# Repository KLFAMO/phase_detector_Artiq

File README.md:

# Phase Detector for Frequencies from 0 to 200 MHz

## Description

This is a phase detector designed to measure phase differences for input frequencies ranging from 0 to approximately 200 MHz. The device includes configurable frequency dividers for each input channel.

An STM32 microcontroller is used to manage the operational parameters of the detector and its components. These settings can be modified via an Ethernet interface by sending specific commands to the device.

## Features

- **Frequency Range**: 0 - 200 MHz (may change, depending on chips availability)
- **Configurable Frequency Dividers** for each input channel
- **STM32 Microcontroller** to manage operational parameters
- **Ethernet Communication** for real-time configuration and monitoring
- **Outputs**:
  - Fast analog output from the phase detector
  - Slow analog output from the phase detector
  - Analog output after passing through a PI controller
- **Standards**: The device is compliant with **Sinara** and **Artic** standards, ensuring compatibility with other systems that adhere to these protocols.

## Communication

The device allows full configuration and monitoring via Ethernet. Users can send commands to the microcontroller to change parameters such as:
- Frequency divider values
- Phase detector settings
- Calibration and diagnostics

## Applications

The phase detector is suitable for a variety of applications, including:
- Laser to optical frequency comb frequency locking
- Laser to laser frequency locking.

## Documentation

Detailed documentation, including schematics, source code, and configuration instructions, will be provided in future releases of the repository.

## commands

`R 1` - read register from `ADDR`, after reading `R` is set to 0

`W 1` - write to register of address `ADDR`, after writing `W` is set to 0

`RV` - red value

`WV` - value to write 

`ADDR` - register address to be red or written

## License

[MIT](https://opensource.org/licenses/MIT)

## Acknowledgments
This work has received funding from the European Partnership on Metrology, co-financed by the European Union’s Horizon Europe Research and Innovation Programme and by the Participating States, under grant number 22IEM01 TOCK.

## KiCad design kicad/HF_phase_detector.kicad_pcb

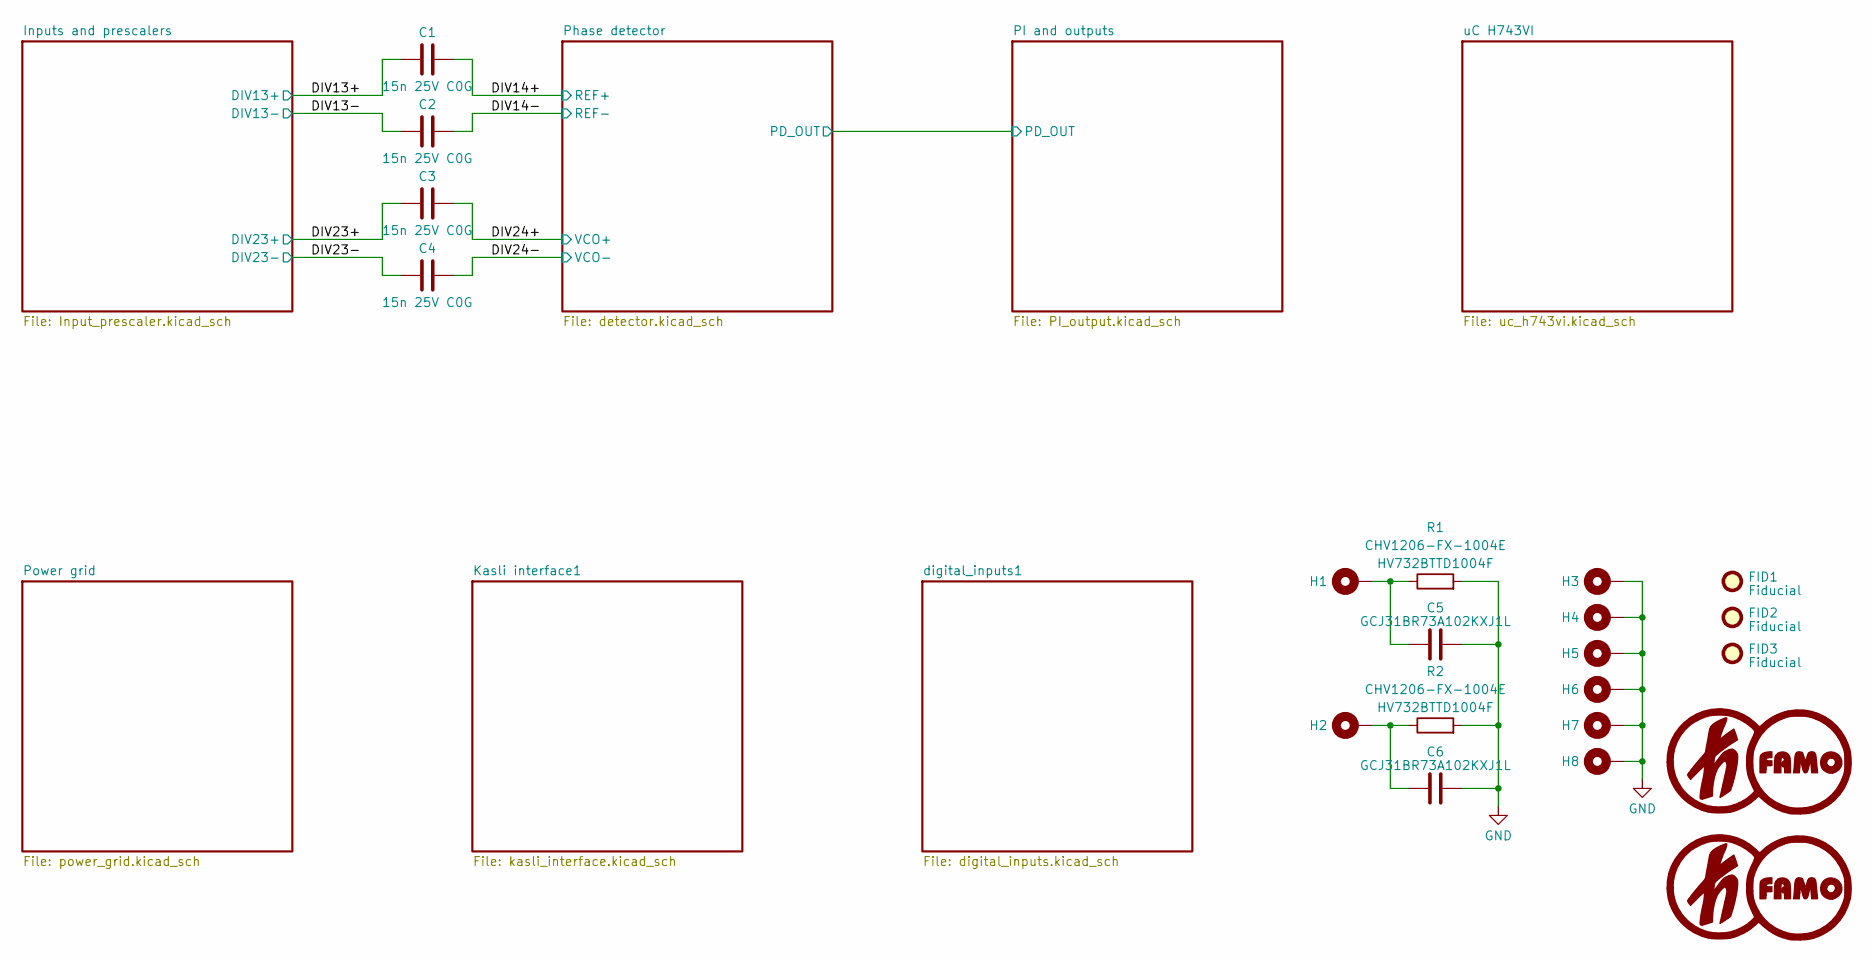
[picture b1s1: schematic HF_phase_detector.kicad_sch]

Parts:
C1, C2, C3, C4: 15n 25V C0G; C_0603_1608Metric
C5, C6: GCJ31BR73A102KXJ1L; C_1206_3216Metric
FID1, FID2, FID3: Fiducial; Fiducial_0.5mm_Mask1.5mm
G1, G2: LOGO; kl_famo_logo_small
H1, H2: MountingHole_Pad; MountingHole_2.7mm_M2.5_DIN965_Pad
H3, H4, H5, H6, H7, H8: MountingHole_Pad; MountingHole_3.2mm_M3_DIN965_Pad
R1, R2: CHV1206-FX-1004E; R_1206_3216Metric

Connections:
/DIV13-: C2.2; also elsewhere on the board
/DIV14-: C2.1; also elsewhere on the board
/DIV23+: C3.2; also elsewhere on the board
/DIV23-: C4.2; also elsewhere on the board
/DIV24+: C3.1; also elsewhere on the board
/DIV24-: C4.1; also elsewhere on the board
unnamed: C5.1, H1.1, R1.1
unnamed: C6.1, H2.1, R2.1

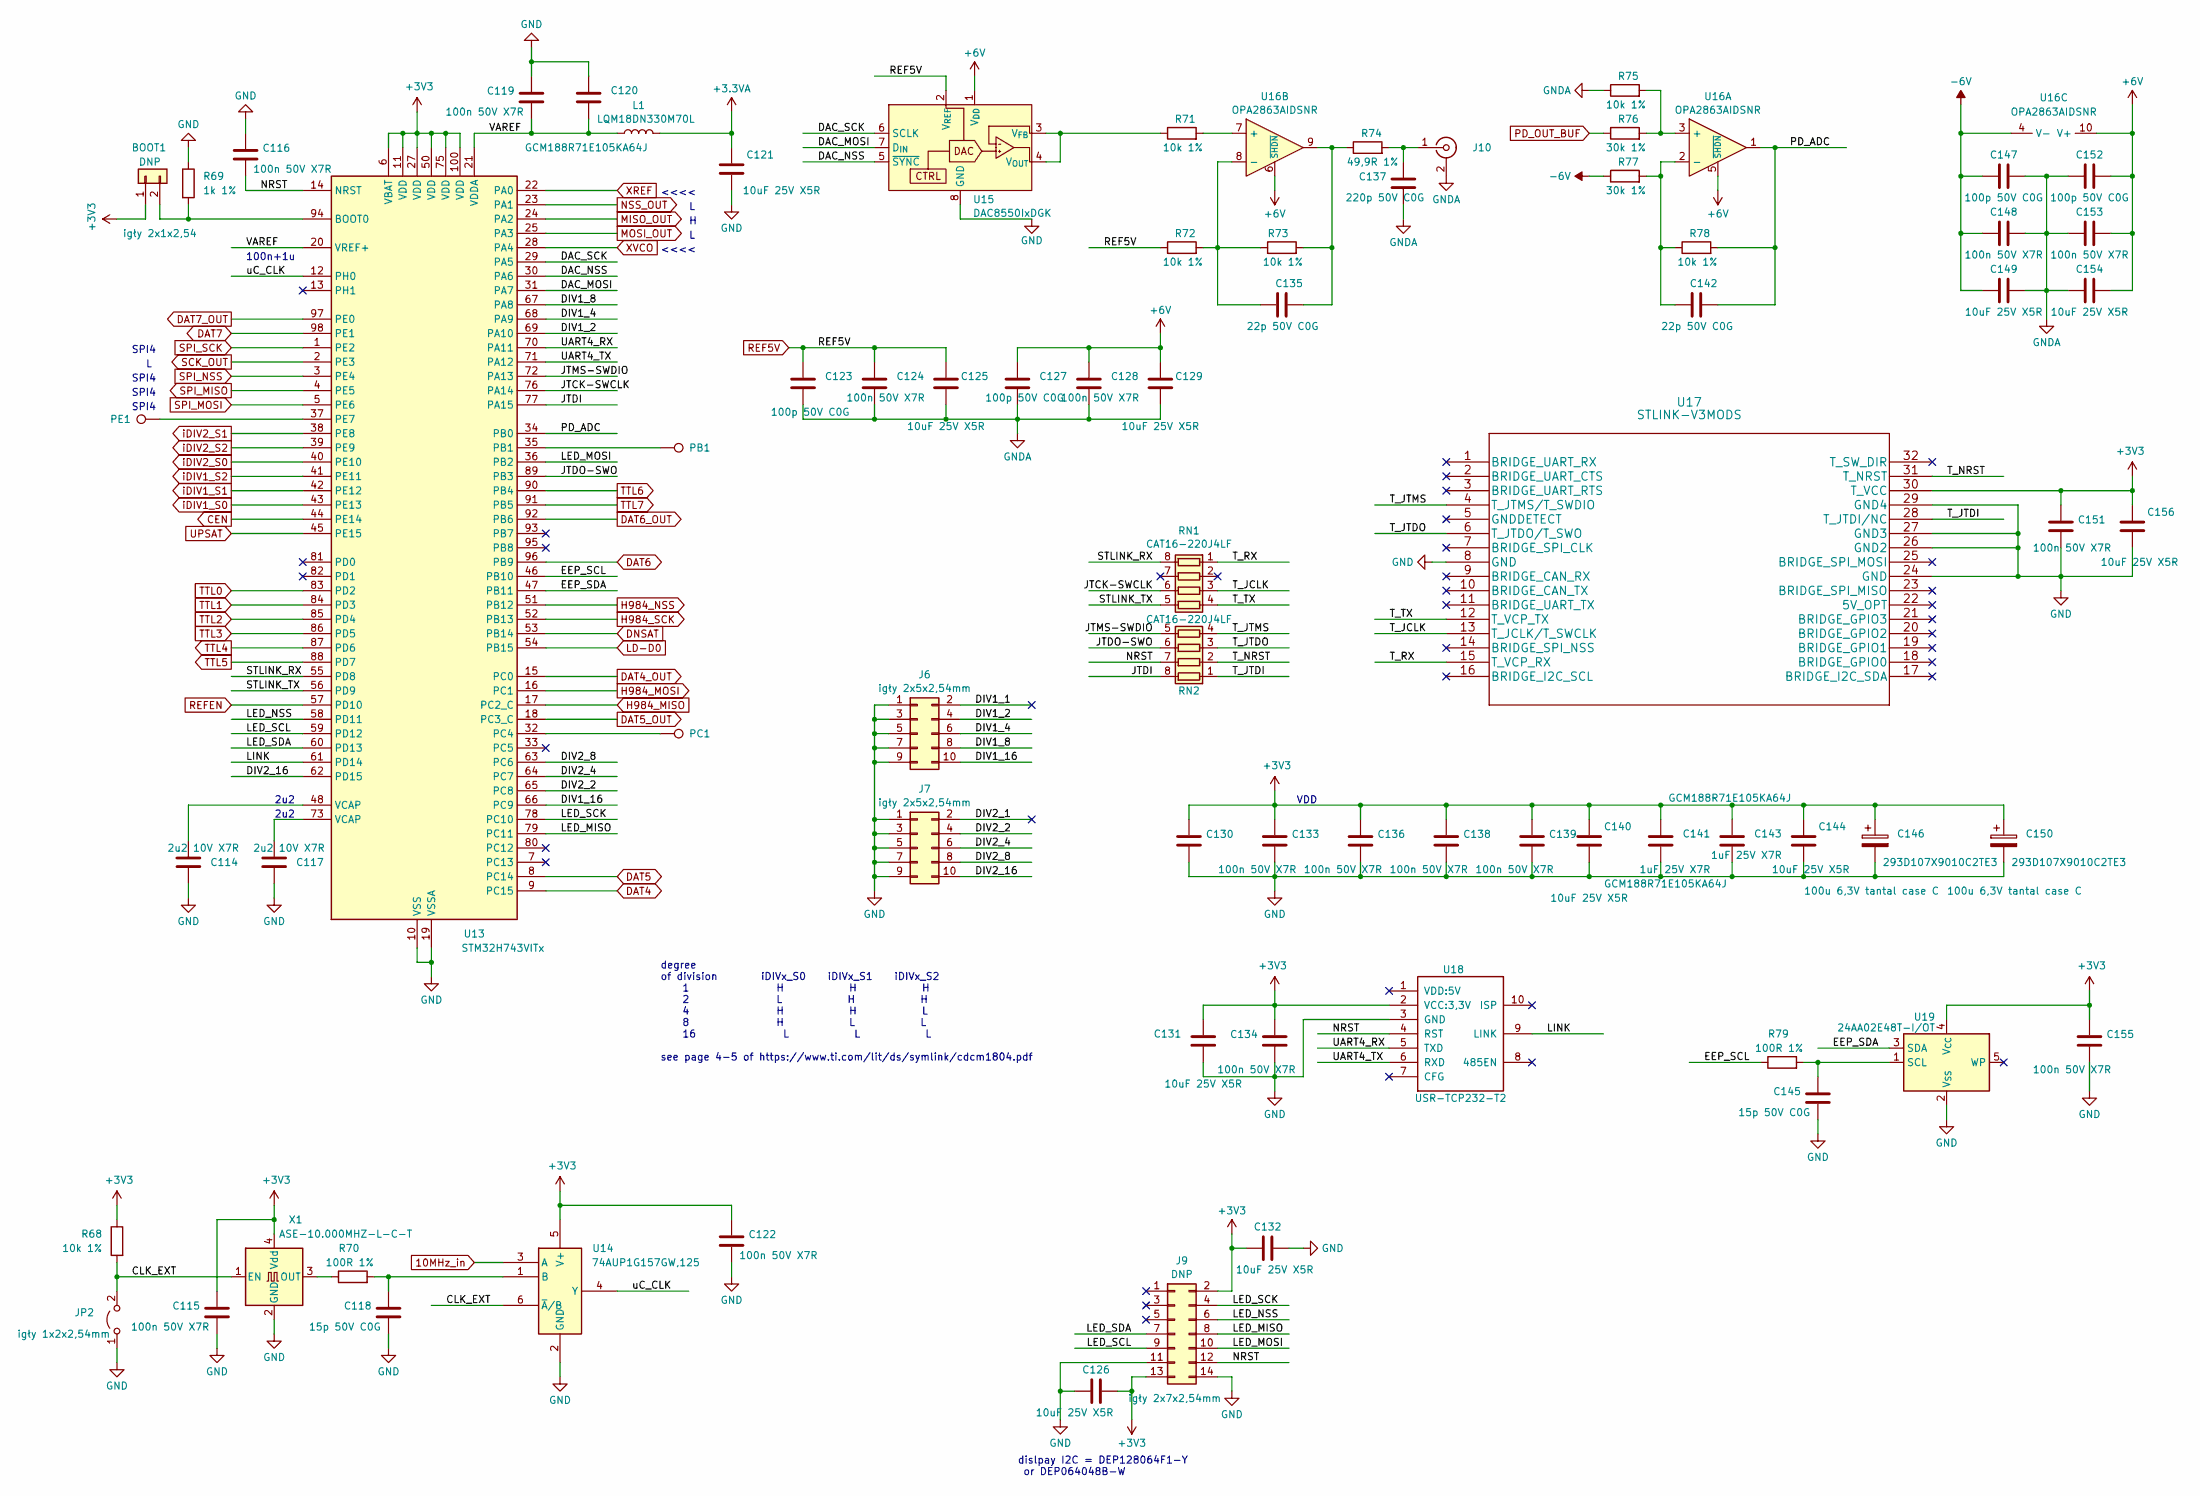
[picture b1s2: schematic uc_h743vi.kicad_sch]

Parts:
BOOT1: DNP; PinHeader_1x02_P2.54mm_Vertical
C114, C117: 2u2 10V X7R; C_0603_1608Metric
C115, C116, C119, C122, C124, C128, C130, C133, C134, C136, C138, C139, C148, C151, C153, C155: 100n 50V X7R; C_0603_1608Metric
C118, C145: 15p 50V C0G; C_0603_1608Metric
C120, C141, C143: GCM188R71E105KA64J; C_0603_1608Metric
C121, C125, C126, C129, C131, C132, C140, C144, C149, C154, C156: GRM188R61E106KA73; C_0603_1608Metric
C123, C127, C147, C152: 100p 50V C0G; C_0603_1608Metric
C135, C142: 22p 50V C0G; C_0603_1608Metric
C137: 220p 50V C0G; C_0603_1608Metric
C146, C150: 293D107X9010C2TE3; CP_EIA-7132-28_AVX-C
J6, J7: igły 2x5x2,54mm; PinHeader_2x05_P2.54mm_Vertical
J9: DNP; PinHeader_2x07_P2.54mm_Vertical
J10: SMA6251A1-3GT50G-50; SMA_Amphenol_132291-12_Vertical
JP2: igły 1x2x2,54mm; PinHeader_1x02_P2.54mm_Vertical
L1: LQM18DN330M70L; L_0603_1608Metric
PB1: TestPoint; TestPoint_THTPad_D1.0mm_Drill0.5mm
PC1: TestPoint; TestPoint_THTPad_D1.0mm_Drill0.5mm
PE1: TestPoint; TestPoint_THTPad_D1.0mm_Drill0.5mm
R68, R71, R72, R73, R75, R78: 10k 1%; R_0603_1608Metric
R69: 1k 1%; R_0603_1608Metric
R70, R79: 100R 1%; R_0603_1608Metric
R74: 49,9R 1%; R_0603_1608Metric
R76, R77: 30k 1%; R_0603_1608Metric
RN1, RN2: CAT16-220J4LF; R_Array_Concave_4x0603
U13: STM32H743VITx; LQFP-100_14x14mm_P0.5mm
U14: 74AUP1G157GW,125; SOT-363_SC-70-6
U15: DAC8550IxDGK; MSOP-8_3x3mm_P0.65mm
U16: OPA2863AIDSNR; DFN-10-1EP_3x3mm_P0.5mm_EP1.65x2.38mm_ThermalVias
U17: STLINK-V3MODS
U18: USR-TCP232-T2; USR-TC232-T2
U19: 24AA02E48T-I/OT; SOT-23-5
X1: ASE-10.000MHZ-L-C-T; Oscillator_SMD_Abracon_ASE-4Pin_3.2x2.5mm

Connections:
10MHz_in: U14.3 (A); also elsewhere on the board
/uC H743VI/CLK_EXT: JP2.2 (B), R68.2, U14.6 (~A/B), X1.1 (EN)
/uC H743VI/DAC_MOSI: U13.31 (PA7), U15.7 (D_{IN})
/uC H743VI/DAC_NSS: U13.30 (PA6), U15.5 (~SYNC)
/uC H743VI/DAC_SCK: U13.29 (PA5), U15.6 (SCLK)
/uC H743VI/DIV1_1: J6.2
/uC H743VI/DIV1_2: J6.4, U13.69 (PA10)
/uC H743VI/DIV1_4: J6.6, U13.68 (PA9)
/uC H743VI/DIV1_8: J6.8, U13.67 (PA8)
/uC H743VI/DIV1_16: J6.10, U13.66 (PC9)
/uC H743VI/DIV2_1: J7.2
/uC H743VI/DIV2_2: J7.4, U13.65 (PC8)
/uC H743VI/DIV2_4: J7.6, U13.64 (PC7)
/uC H743VI/DIV2_8: J7.8, U13.63 (PC6)
/uC H743VI/DIV2_16: J7.10, U13.62 (PD15)
/uC H743VI/EEP_SCL: R79.1, U13.46 (PB10)
/uC H743VI/EEP_SDA: U13.47 (PB11), U19.3 (SDA)
/uC H743VI/JTCK-SWCLK: RN1.6 (R3.2), U13.76 (PA14)
/uC H743VI/JTDI: RN2.8 (R1.2), U13.77 (PA15)
/uC H743VI/JTDO-SWO: RN2.6 (R3.2), U13.89 (PB3)
/uC H743VI/JTMS-SWDIO: RN2.5 (R4.2), U13.72 (PA13)
/uC H743VI/LED_MISO: J9.8, U13.79 (PC11)
/uC H743VI/LED_MOSI: J9.10, U13.36 (PB2)
/uC H743VI/LED_NSS: J9.6, U13.58 (PD11)
/uC H743VI/LED_SCK: J9.4, U13.78 (PC10)
/uC H743VI/LED_SCL: J9.9, U13.59 (PD12)
/uC H743VI/LED_SDA: J9.7, U13.60 (PD13)
/uC H743VI/LINK: U13.61 (PD14), U18.9 (LINK)
/uC H743VI/NRST: C116.2, J9.12, RN2.7 (R2.2), U13.14 (NRST), U18.4 (RST)
/uC H743VI/STLINK_RX: RN1.8 (R1.2), U13.55 (PD8)
/uC H743VI/STLINK_TX: RN1.5 (R4.2), U13.56 (PD9)
/uC H743VI/T_JCLK: RN1.3 (R3.1), U17.13 (T_JCLK/T_SWCLK)
/uC H743VI/T_JTDI: RN2.1 (R1.1), U17.28 (T_JTDI/NC)
/uC H743VI/T_JTDO: RN2.3 (R3.1), U17.6 (T_JTDO/T_SWO)
/uC H743VI/T_JTMS: RN2.4 (R4.1), U17.4 (T_JTMS/T_SWDIO)
/uC H743VI/T_NRST: RN2.2 (R2.1), U17.31 (T_NRST)
/uC H743VI/T_RX: RN1.1 (R1.1), U17.15 (T_VCP_RX)
/uC H743VI/T_TX: RN1.4 (R4.1), U17.12 (T_VCP_TX)
/uC H743VI/UART4_RX: U13.70 (PA11), U18.5 (TXD)
/uC H743VI/UART4_TX: U13.71 (PA12), U18.6 (RXD)
/uC H743VI/uC_CLK: U13.12 (PH0), U14.4 (Y)
CEN: U13.44 (PE14); also elsewhere on the board
DAT4: U13.9 (PC15); also elsewhere on the board
DAT4_OUT: U13.15 (PC0); also elsewhere on the board
DAT5: U13.8 (PC14); also elsewhere on the board
DAT5_OUT: U13.18 (PC3_C); also elsewhere on the board
DAT6: U13.96 (PB9); also elsewhere on the board
DAT6_OUT: U13.92 (PB6); also elsewhere on the board
DAT7: U13.98 (PE1); also elsewhere on the board
DAT7_OUT: U13.97 (PE0); also elsewhere on the board
DNSAT: U13.53 (PB14); also elsewhere on the board
H984_MISO: U13.17 (PC2_C); also elsewhere on the board
H984_MOSI: U13.16 (PC1); also elsewhere on the board
H984_NSS: U13.51 (PB12); also elsewhere on the board
H984_SCK: U13.52 (PB13); also elsewhere on the board
LD-D0: U13.54 (PB15); also elsewhere on the board
MISO_OUT: U13.24 (PA2); also elsewhere on the board
MOSI_OUT: U13.25 (PA3); also elsewhere on the board
NSS_OUT: U13.23 (PA1); also elsewhere on the board
unnamed: BOOT1.2, R69.2, U13.94 (BOOT0)
unnamed: C114.2, U13.48 (VCAP)
unnamed: C117.2, U13.73 (VCAP)
unnamed: C135.2, R73.2, R74.1, U16.9
unnamed: C137.2, J10.1 (In), R74.2
unnamed: PB1.1, U13.35 (PB1)
unnamed: PC1.1, U13.32 (PC4)
unnamed: PE1.1, U13.37 (PE7)
unnamed: C118.1, R70.2, U14.1 (B)
unnamed: R71.1, U15.3 (V_{FB}), U15.4 (V_{OUT})
unnamed: R75.2, R76.2, U16.3 (+)
unnamed: R71.2, U16.7 (+)
unnamed: C135.1, R72.2, R73.1, U16.8 (-)
unnamed: C145.1, R79.2, U19.1 (SCL)
unnamed: R70.1, X1.3 (OUT)
PD_OUT_BUF: R76.1; also elsewhere on the board
REF5V: C123.2, C124.2, C125.2, R72.1, U15.2 (V_{REF}); also elsewhere on the board
REFEN: U13.57 (PD10); also elsewhere on the board
SCK_OUT: U13.2 (PE3); also elsewhere on the board
SPI_MISO: U13.4 (PE5); also elsewhere on the board
SPI_MOSI: U13.5 (PE6); also elsewhere on the board
SPI_NSS: U13.3 (PE4); also elsewhere on the board
SPI_SCK: U13.1 (PE2); also elsewhere on the board
TTL0: U13.83 (PD2); also elsewhere on the board
TTL1: U13.84 (PD3); also elsewhere on the board
TTL2: U13.85 (PD4); also elsewhere on the board
TTL3: U13.86 (PD5); also elsewhere on the board
TTL4: U13.87 (PD6); also elsewhere on the board
TTL5: U13.88 (PD7); also elsewhere on the board
TTL6: U13.90 (PB4); also elsewhere on the board
TTL7: U13.91 (PB5); also elsewhere on the board
UPSAT: U13.45 (PE15); also elsewhere on the board
XREF: U13.22 (PA0); also elsewhere on the board
XVCO: U13.28 (PA4); also elsewhere on the board
iDIV1_S0: U13.43 (PE13); also elsewhere on the board
iDIV1_S1: U13.42 (PE12); also elsewhere on the board
iDIV1_S2: U13.41 (PE11); also elsewhere on the board
iDIV2_S0: U13.40 (PE10); also elsewhere on the board
iDIV2_S1: U13.38 (PE8); also elsewhere on the board
iDIV2_S2: U13.39 (PE9); also elsewhere on the board

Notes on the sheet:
VDD
2u2
<<<<
dislpay I2C = DEP128064F1-Y or DEP064048B-W
SPI4
100n+1u
degree of division iDIVx_S0 iDIVx_S1 iDIVx_S2 1 H H H 2 L H H 4 H H L 8 H L L 16 L L L see page 4-5 of https://www.ti.com/lit/ds/symlink/cdcm1804.pdf

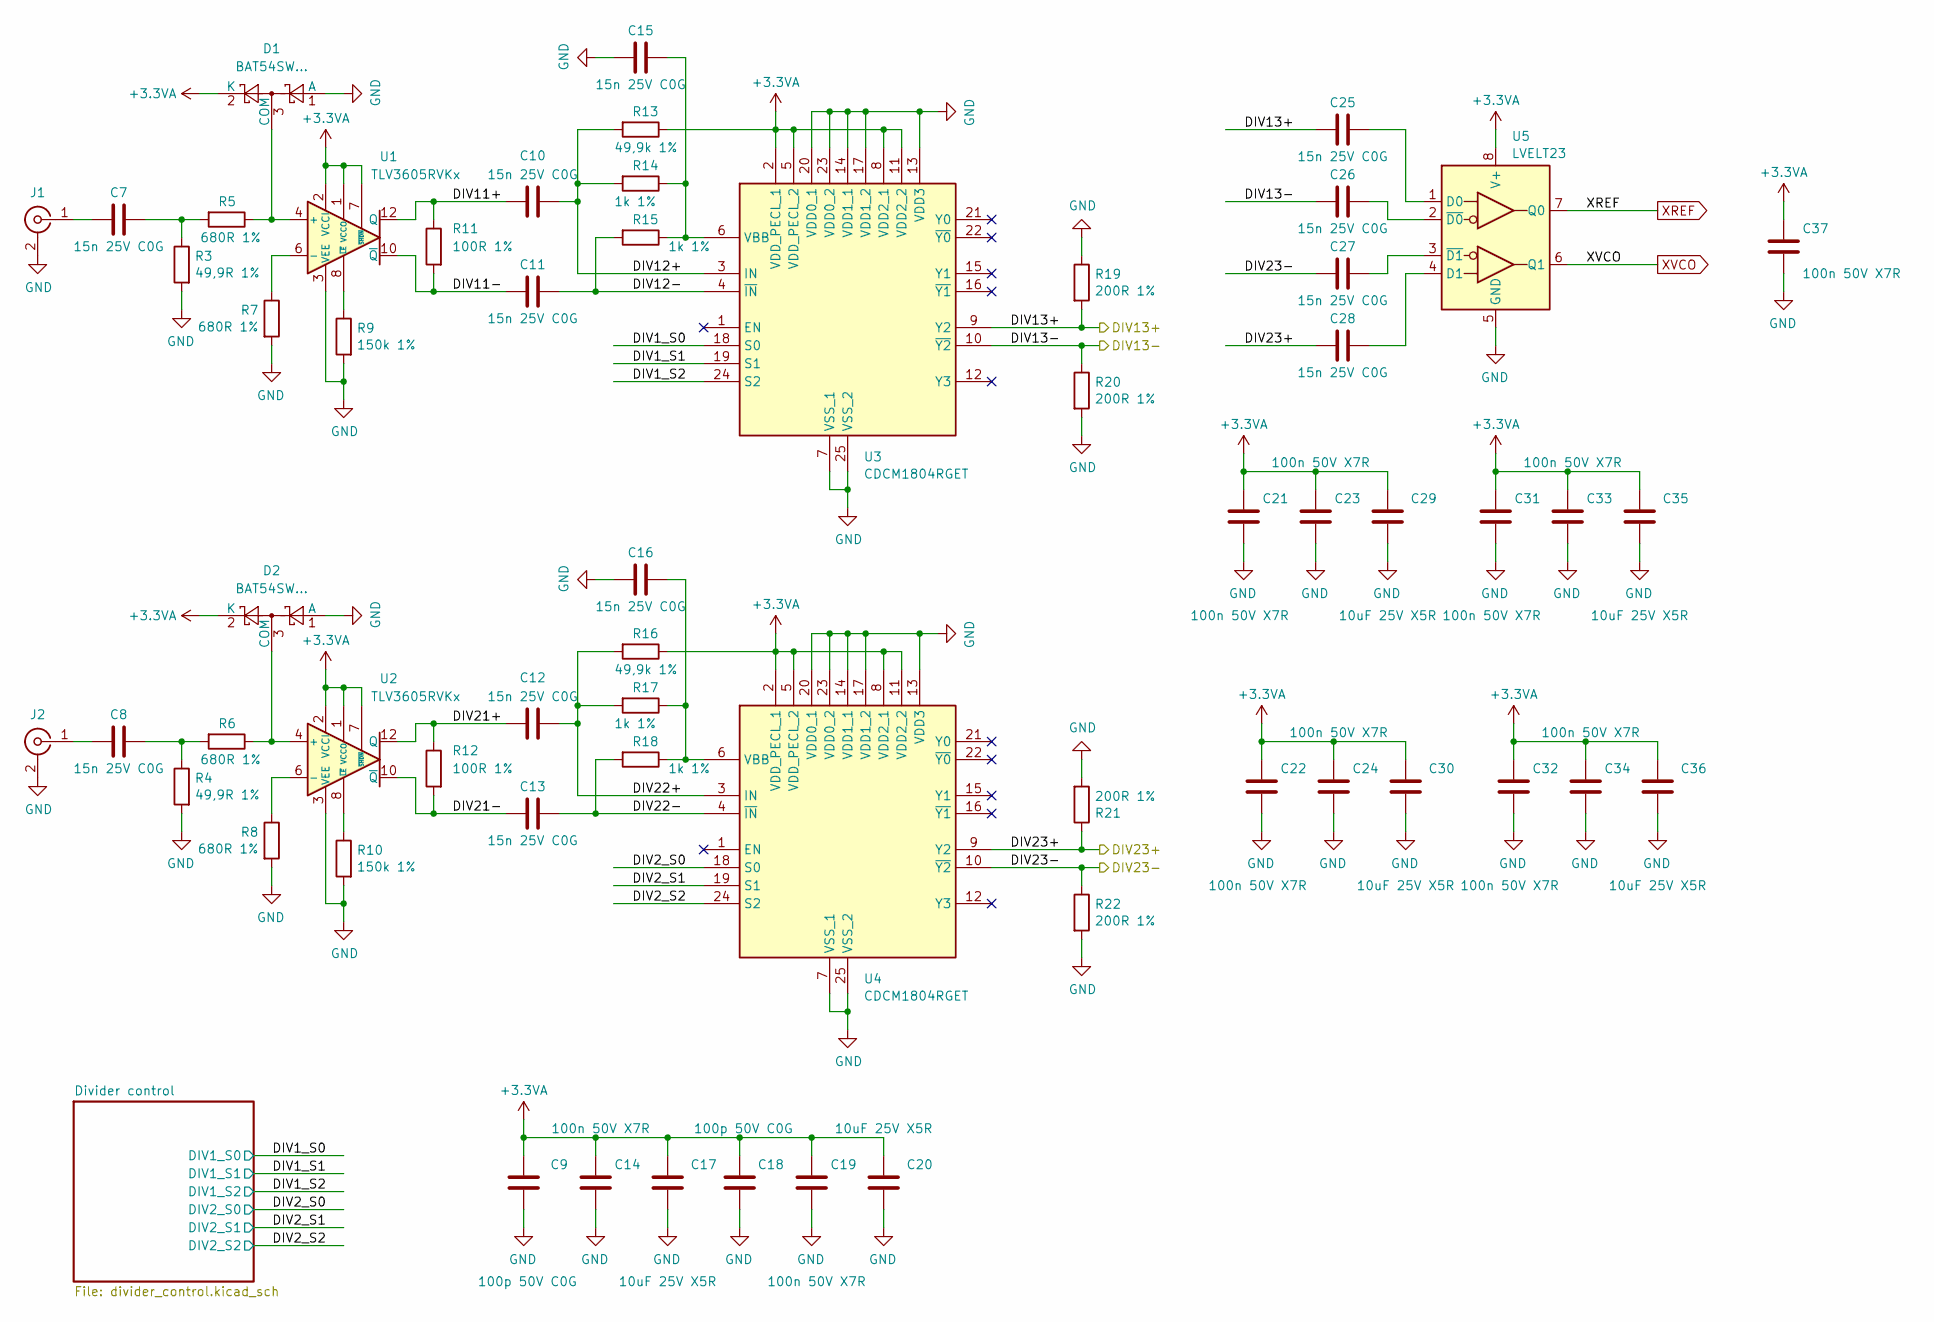
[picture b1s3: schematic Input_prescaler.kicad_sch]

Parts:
C7, C8, C10, C11, C12, C13, C15, C16, C25, C26, C27, C28: 15n 25V C0G; C_0603_1608Metric
C9, C18: 100p 50V C0G; C_0603_1608Metric
C14, C19, C21, C22, C23, C24, C31, C32, C33, C34, C37: 100n 50V X7R; C_0603_1608Metric
C17, C20, C29, C30, C35, C36: GRM188R61E106KA73; C_0603_1608Metric
D1, D2: BAT54SW...; SOT-323_SC-70
J1, J2: RF2-49B-T-00-50-G-HDW; SMA_Amphenol_132203-12_Horizontal
R3, R4: 49,9R 1%; R_0603_1608Metric
R5, R6, R7, R8: 680R 1%; R_0603_1608Metric
R9, R10: 150k 1%; R_0603_1608Metric
R11, R12: 100R 1%; R_0603_1608Metric
R13, R16: 49,9k 1%; R_0603_1608Metric
R14, R15, R17, R18: 1k 1%; R_0603_1608Metric
R19, R20, R21, R22: 200R 1%; R_0603_1608Metric
U1, U2: TLV3605RVKx; QFN-12-1EP_3x3mm_P0.5mm_EP1.65x1.65mm_ThermalVias
U3, U4: CDCM1804RGET; QFN-24-1EP_4x4mm_P0.5mm_EP2.15x2.15mm_ThermalVias
U5: LVELT23; MSOP-8_3x3mm_P0.65mm

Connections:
/DIV13-: C26.2, R20.1, U3.10 (~Y2); also elsewhere on the board
/DIV23+: C28.2, R21.1, U4.9 (Y2); also elsewhere on the board
/DIV23-: C27.2, R22.1, U4.10 (~Y2); also elsewhere on the board
/Inputs and prescalers/DIV1_S0: U3.18 (S0); also elsewhere on the board
/Inputs and prescalers/DIV1_S1: U3.19 (S1); also elsewhere on the board
/Inputs and prescalers/DIV1_S2: U3.24 (S2); also elsewhere on the board
/Inputs and prescalers/DIV2_S0: U4.18 (S0); also elsewhere on the board
/Inputs and prescalers/DIV2_S1: U4.19 (S1); also elsewhere on the board
/Inputs and prescalers/DIV2_S2: U4.24 (S2); also elsewhere on the board
/Inputs and prescalers/DIV11+: C10.2, R11.1, U1.12 (Q)
/Inputs and prescalers/DIV11-: C11.2, R11.2, U1.10 (~Q)
/Inputs and prescalers/DIV12+: C10.1, R13.2, R14.2, U3.3 (IN)
/Inputs and prescalers/DIV12-: C11.1, R15.2, U3.4 (~IN)
/Inputs and prescalers/DIV21+: C12.2, R12.1, U2.12 (Q)
/Inputs and prescalers/DIV21-: C13.2, R12.2, U2.10 (~Q)
/Inputs and prescalers/DIV22+: C12.1, R16.2, R17.2, U4.3 (IN)
/Inputs and prescalers/DIV22-: C13.1, R18.2, U4.4 (~IN)
unnamed: C7.1, R3.1, R5.2
unnamed: C8.1, R4.1, R6.2
unnamed: D1.3 (COM), R5.1, U1.4 (+)
unnamed: D2.3 (COM), R6.1, U2.4 (+)
unnamed: C8.2, J2.1 (In)
unnamed: R7.1, U1.6 (-)
unnamed: R9.1, U1.8 (~LE)
unnamed: R8.1, U2.6 (-)
unnamed: R10.1, U2.8 (~LE)
unnamed: C15.1, R14.1, R15.1, U3.6 (VBB)
unnamed: C16.1, R17.1, R18.1, U4.6 (VBB)
unnamed: C25.1, U5.1 (D0)
unnamed: C28.1, U5.4 (D1)
unnamed: C26.1, U5.2 (~D0)
unnamed: C27.1, U5.3 (~D1)
XREF: U5.7 (Q0); also elsewhere on the board
XVCO: U5.6 (Q1); also elsewhere on the board

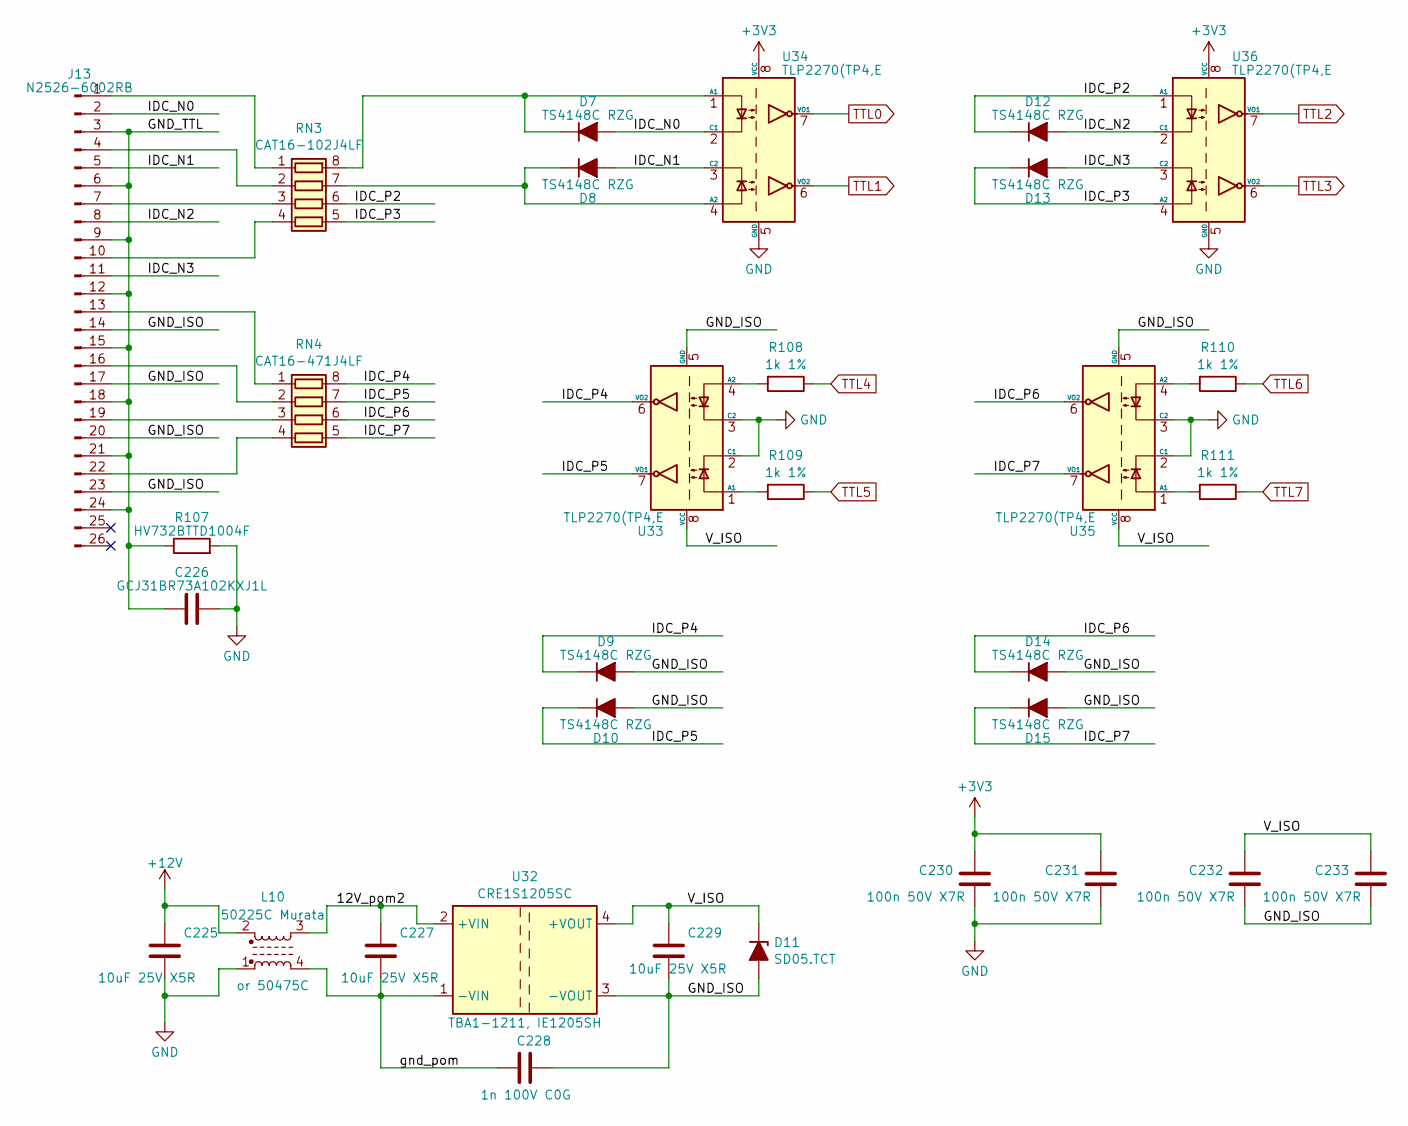
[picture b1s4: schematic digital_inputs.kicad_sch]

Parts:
C225, C227, C229: GRM188R61E106KA73; C_0603_1608Metric
C226: GCJ31BR73A102KXJ1L; C_1206_3216Metric
C228: 1n 100V C0G; C_0805_2012Metric
C230, C231, C232, C233: 100n 50V X7R; C_0603_1608Metric
D7, D8, D9, D10, D12, D13, D14, D15: TS4148C RZG; D_0603_1608Metric
D11: SD05.TCT; D_SOD-323
J13: N2526-6002RB; IDC-Header_2x13_P2.54mm_Vertical
L10: 50225C Murata; L_CommonMode_Murata_5000
R107: HV732BTTD1004F; R_1206_3216Metric
R108, R109, R110, R111: 1k 1%; R_0603_1608Metric
RN3: CAT16-102J4LF; R_Array_Concave_4x0603
RN4: CAT16-471J4LF; R_Array_Concave_4x0603
U32: CRE1S1205SC; Converter_DCDC_Murata_CRE1xxxxxxSC_THT
U33, U34, U35, U36: TLP2270(TP4,E; SOIC-8_7.5x5.85mm_P1.27mm

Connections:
/digital_inputs1/12V_pom2: C227.2, L10.3, U32.2 (+VIN)
/digital_inputs1/GND_ISO: C228.1, C229.1, C232.2, C233.2, D9.2 (A), D10.2 (A), D11.2 (A), D14.2 (A), D15.2 (A), J13.14, J13.17, J13.20, J13.23, U32.3 (-VOUT), U33.5 (GND), U35.5 (GND)
/digital_inputs1/GND_TTL: C226.1, J13.3, J13.6, J13.9, J13.12, J13.15, J13.18, J13.21, J13.24, R107.1
/digital_inputs1/IDC_N0: D7.2 (A), J13.2, U34.2 (C1)
/digital_inputs1/IDC_N1: D8.2 (A), J13.5, U34.3 (C2)
/digital_inputs1/IDC_N2: D12.2 (A), J13.8, U36.2 (C1)
/digital_inputs1/IDC_N3: D13.2 (A), J13.11, U36.3 (C2)
/digital_inputs1/IDC_P2: D12.1 (K), RN3.6 (R3.2), U36.1 (A1)
/digital_inputs1/IDC_P3: D13.1 (K), RN3.5 (R4.2), U36.4 (A2)
/digital_inputs1/IDC_P4: D9.1 (K), RN4.8 (R1.2), U33.6 (VO2)
/digital_inputs1/IDC_P5: D10.1 (K), RN4.7 (R2.2), U33.7 (VO1)
/digital_inputs1/IDC_P6: D14.1 (K), RN4.6 (R3.2), U35.6 (VO2)
/digital_inputs1/IDC_P7: D15.1 (K), RN4.5 (R4.2), U35.7 (VO1)
/digital_inputs1/V_ISO: C229.2, C232.1, C233.1, D11.1 (K), U32.4 (+VOUT), U33.8 (VCC), U35.8 (VCC)
/digital_inputs1/gnd_pom: C227.1, C228.2, L10.4, U32.1 (-VIN)
unnamed: D7.1 (K), RN3.8 (R1.2), U34.1 (A1)
unnamed: D8.1 (K), RN3.7 (R2.2), U34.4 (A2)
unnamed: J13.1, RN3.1 (R1.1)
unnamed: J13.4, RN3.2 (R2.1)
unnamed: J13.7, RN3.3 (R3.1)
unnamed: J13.10, RN3.4 (R4.1)
unnamed: J13.13, RN4.1 (R1.1)
unnamed: J13.16, RN4.2 (R2.1)
unnamed: J13.19, RN4.3 (R3.1)
unnamed: J13.22, RN4.4 (R4.1)
unnamed: R109.2, U33.1 (A1)
unnamed: R108.2, U33.4 (A2)
unnamed: R111.2, U35.1 (A1)
unnamed: R110.2, U35.4 (A2)
TTL0: U34.7 (VO1); also elsewhere on the board
TTL1: U34.6 (VO2); also elsewhere on the board
TTL2: U36.7 (VO1); also elsewhere on the board
TTL3: U36.6 (VO2); also elsewhere on the board
TTL4: R108.1; also elsewhere on the board
TTL5: R109.1; also elsewhere on the board
TTL6: R110.1; also elsewhere on the board
TTL7: R111.1; also elsewhere on the board

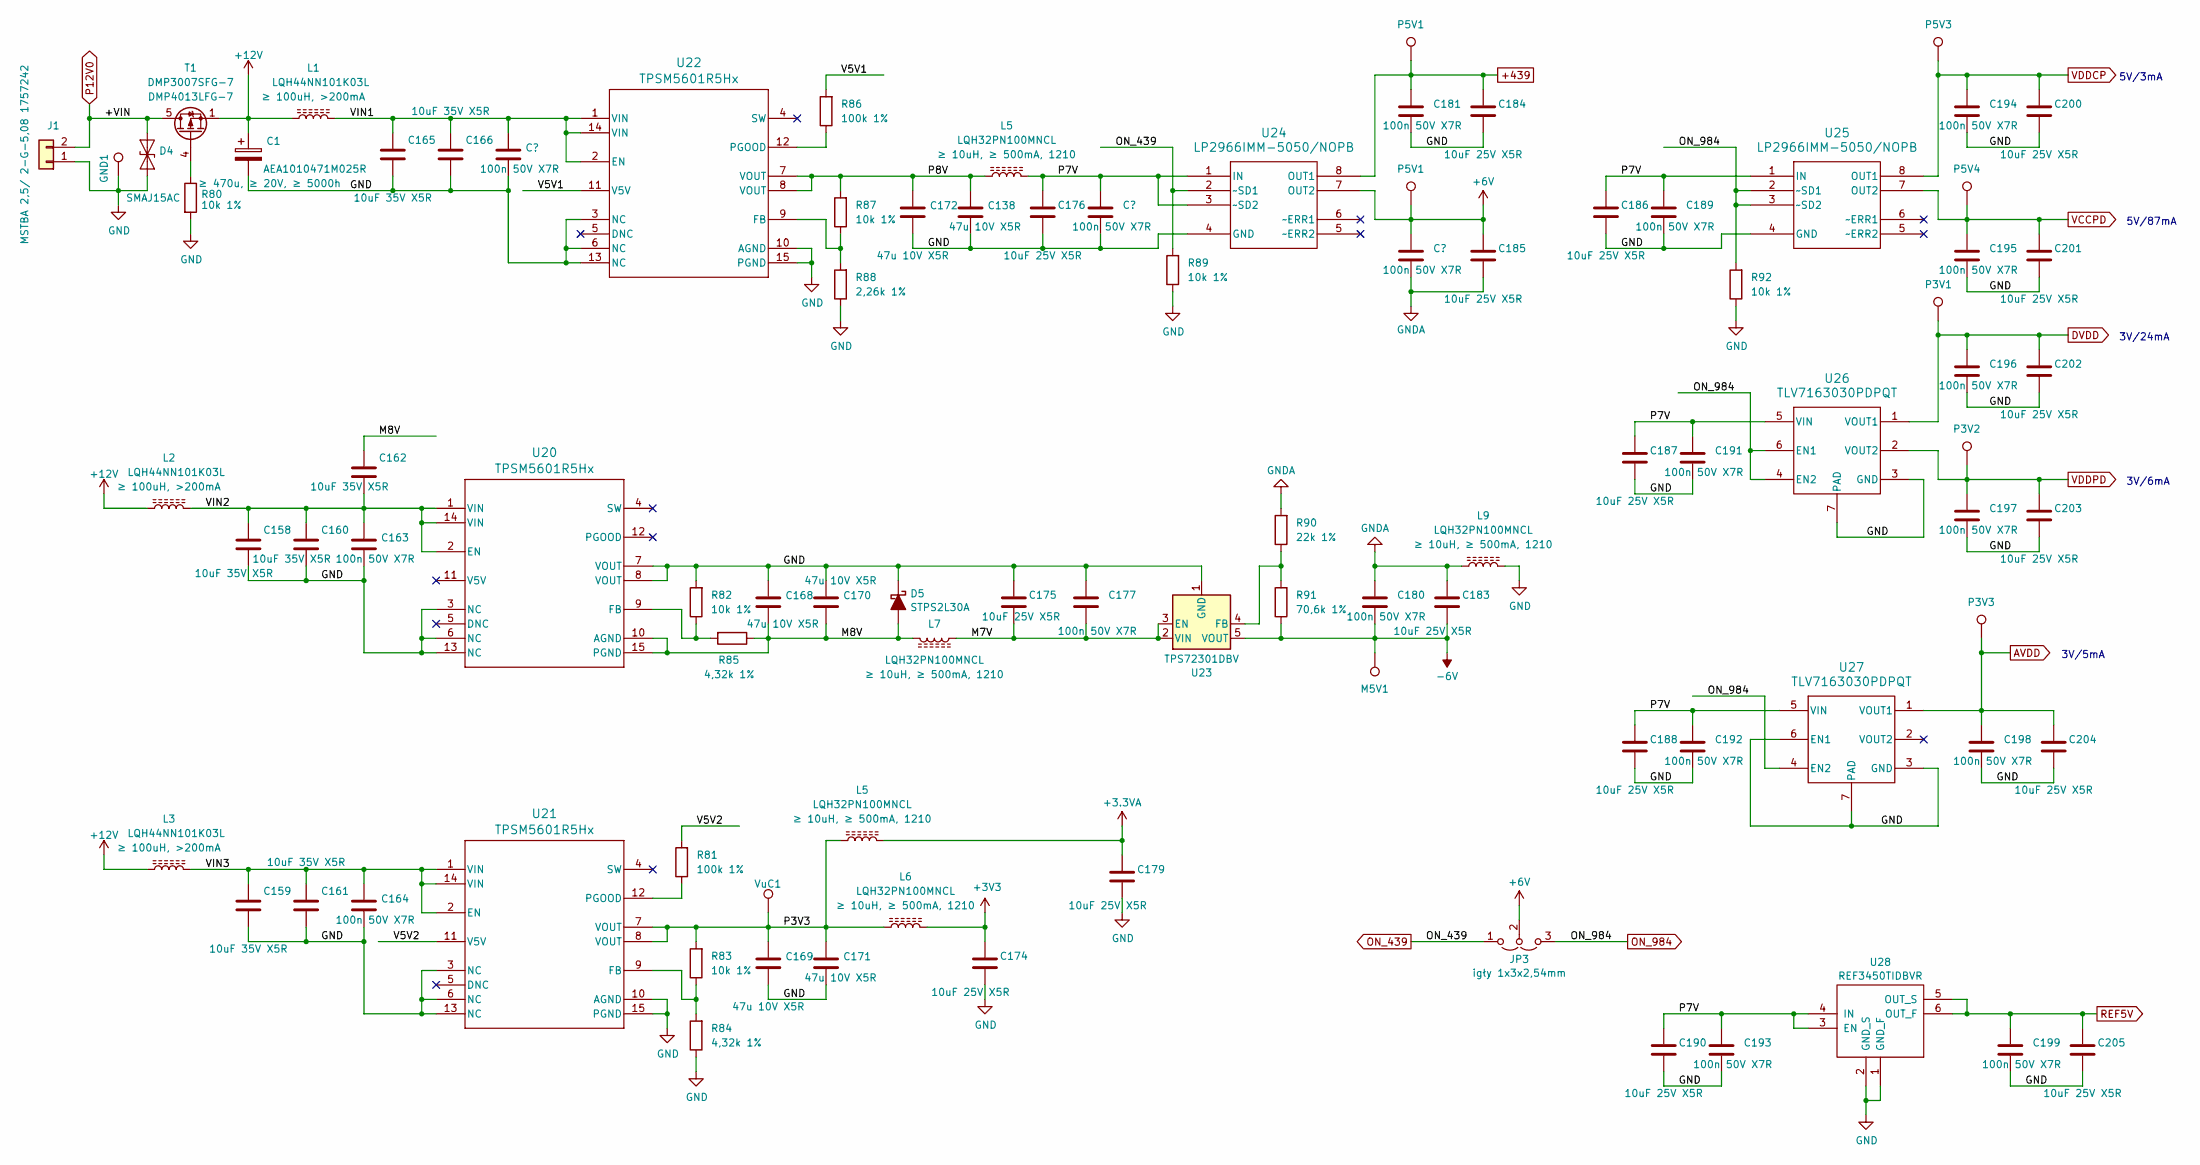
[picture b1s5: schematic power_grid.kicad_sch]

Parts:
C1: AEA1010471M025R; CP_Elec_10x10
C134, C142, C147, C163, C164, C177, C180, C181, C189, C191, C192, C193, C194, C195, C196, C197, C198, C199: 100n 50V X7R; C_0603_1608Metric
C138, C168, C169, C170, C171, C172: GRM31CR61A476KE15L; C_1206_3216Metric
C158, C159, C160, C161, C162, C165, C166: GRM188R6YA106MA73; C_0603_1608Metric
C174, C175, C176, C179, C183, C184, C185, C186, C187, C188, C190, C200, C201, C202, C203, C204, C205: GRM188R61E106KA73; C_0603_1608Metric
D4: SMAJ15AC; D_SMA
D5: STPS2L30A; D_SMA
GND1: TestPoint; TestPoint_Bridge_Pitch2.54mm_Drill1.0mm
J1: MSTBA 2,5/ 2-G-5,08 1757242; PhoenixContact_MSTBA_2,5_2-G-5,08_1x02_P5.08mm_Horizontal
JP3: igły 1x3x2,54mm; PinHeader_1x03_P2.54mm_Vertical
L1, L2, L3: LQH44NN101K03L; L_MURATA_LQH44
L5, L6, L7, L9: LQH32PN100MNCL; L_1210_3225Metric
M5V1: TestPoint; TestPoint_THTPad_1.5x1.5mm_Drill0.7mm
P3V1, P3V2, P3V3, P5V1, P5V3, P5V4: TestPoint; TestPoint_THTPad_1.5x1.5mm_Drill0.7mm
R80, R82, R83, R87, R89, R92: 10k 1%; R_0603_1608Metric
R81, R86: 100k 1%; R_0603_1608Metric
R84, R85: 4,32k 1%; R_0603_1608Metric
R88: 2,26k 1%; R_0603_1608Metric
R90: 22k 1%; R_0603_1608Metric
R91: 70,6k 1%; R_0603_1608Metric
T1: DMP3007SFG-7; Diodes_PowerDI3333-8
U20, U21, U22: TPSM5601R5Hx; 15-B3QFN (5x5,5)
U23: TPS72301DBV; SOT-23-5
U24, U25: LP2966IMM-5050/NOPB; VSSOP-8_3.0x3.0mm_P0.65mm
U26, U27: TLV7163030PDPQT; DFN-6-1EP_1.2x1.2mm_P0.4mm_EP0.3x0.94mm_ff
U28: REF3450TIDBVR; SOT-23-6
VuC1: TestPoint; TestPoint_THTPad_1.5x1.5mm_Drill0.7mm

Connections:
/Power grid/M7V: C175.1, C177.1, L7.2, U23.2 (VIN), U23.3 (EN)
/Power grid/M8V: C162.2, C168.2, C170.2, D5.2 (A), L7.1, R85.1, U20.10 (AGND), U20.15 (PGND)
/Power grid/V5V1: R86.2, U22.11 (V5V)
/Power grid/V5V2: R81.2, U21.11 (V5V)
/Power grid/VIN2: C158.2, C160.2, C162.1, C163.2, L2.2, U20.1 (VIN), U20.2 (EN), U20.14 (VIN)
/Power grid/VIN3: C159.2, C161.2, C164.2, L3.2, U21.1 (VIN), U21.2 (EN), U21.14 (VIN)
AVDD: C198.2, C204.2, P3V3.1, U27.1 (VOUT1); also elsewhere on the board
DVDD: C196.2, C202.2, P3V1.1, U26.1 (VOUT1); also elsewhere on the board
unnamed: R80.1, T1.4 (G)
unnamed: R82.1, R85.2, U20.9 (FB)
unnamed: R83.1, R84.2, U21.9 (FB)
unnamed: R81.1, U21.12 (PGOOD)
unnamed: R87.1, R88.2, U22.9 (FB)
unnamed: R86.1, U22.12 (PGOOD)
unnamed: R90.1, R91.2, U23.4 (FB)
ON_439: JP3.1 (A), R89.2, U24.2 (~SD1); also elsewhere on the board
ON_984: JP3.3 (B), R92.2, U25.2 (~SD1), U25.3 (~SD2), U26.4 (EN2), U26.6 (EN1), U27.4 (EN2); also elsewhere on the board
REF5V: C199.2, C205.2, U28.5 (OUT_S), U28.6 (OUT_F); also elsewhere on the board
VCCPD: C195.2, C201.2, P5V4.1, U25.7 (OUT2); also elsewhere on the board
VDDCP: C194.2, C200.2, P5V3.1, U25.8 (OUT1); also elsewhere on the board
VDDPD: C197.2, C203.2, P3V2.1, U26.2 (VOUT2); also elsewhere on the board

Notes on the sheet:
5V/3mA
3V/6mA
5V/87mA
3V/5mA
3V/24mA
